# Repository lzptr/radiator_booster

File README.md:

# Radiator Booster
ESP32C3 based fan control board for a modular  [3d printed radiator booster](https://www.printables.com/model/329566-heizkorperverstarker-mit-magnethalterung-radiator-?lang=de) based on this design.
The idea is to use ESPHome with Home Assistant to turn on up to 5 radiator booster fans, when my smart thermostats are turning on, and use a Home Assistant automation to keep them running for an hour and automatically shut them off after that.

For an interactive KiCad experience see:
[Radiator Booster](https://kicanvas.org/?github=https://github.com/lzptr/radiator_booster/tree/main/hardware).

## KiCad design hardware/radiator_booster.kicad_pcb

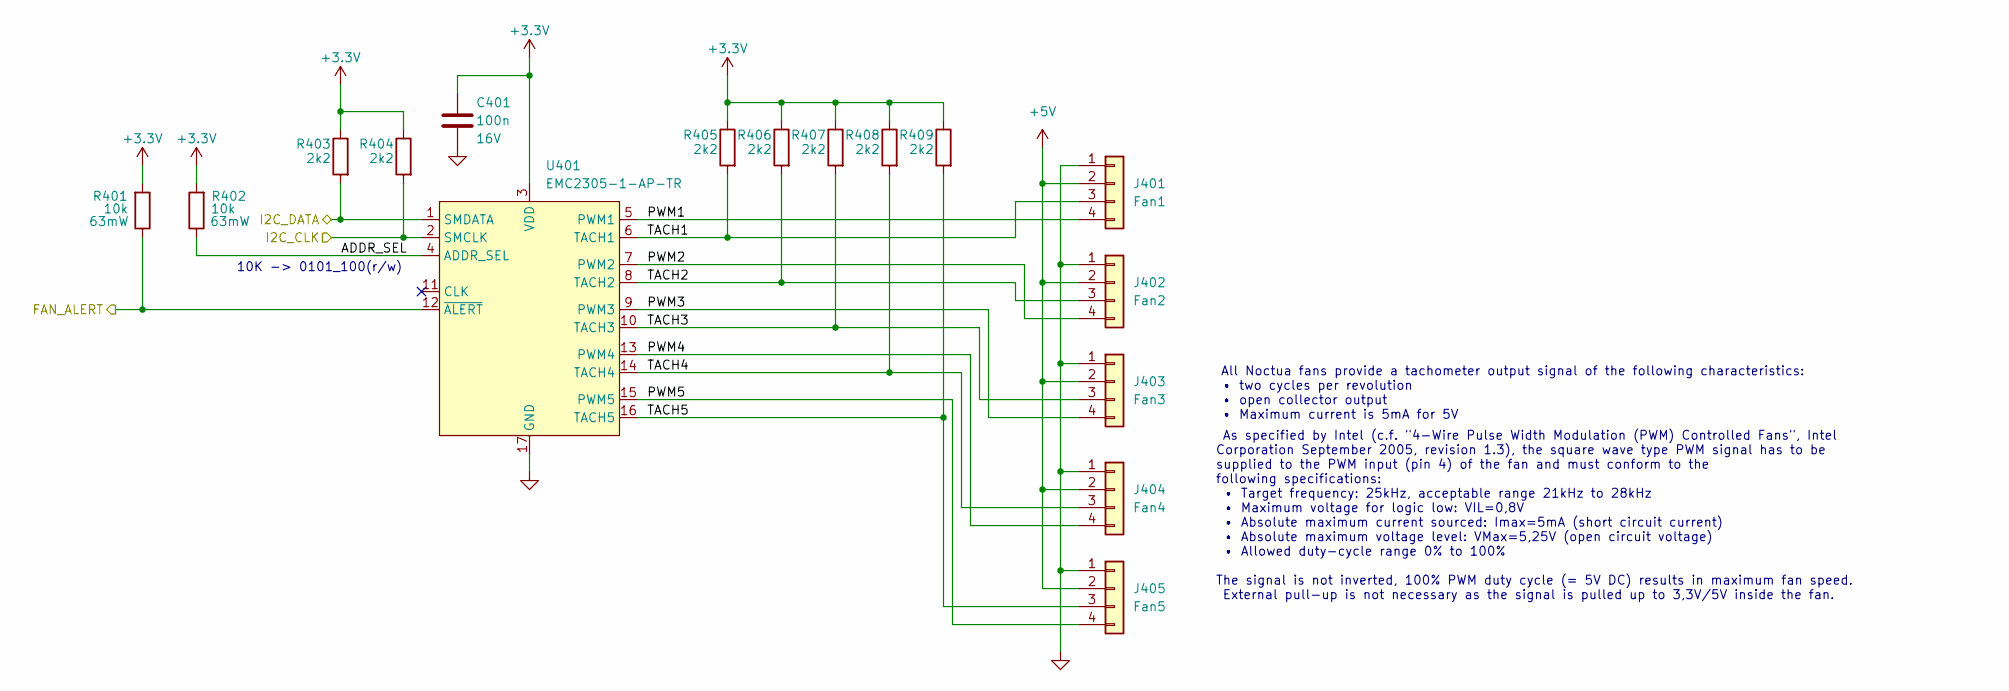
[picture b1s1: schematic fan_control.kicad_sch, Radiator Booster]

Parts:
C401: 100n; C_0402_1005Metric; Rating 16V; MPN C1525
J401: Fan1; FanPinHeader_1x04_P2.54mm_Vertical; MPN C240840
J402: Fan2; FanPinHeader_1x04_P2.54mm_Vertical; MPN C240840
J403: Fan3; FanPinHeader_1x04_P2.54mm_Vertical; MPN C240840
J404: Fan4; FanPinHeader_1x04_P2.54mm_Vertical; MPN C240840
J405: Fan5; FanPinHeader_1x04_P2.54mm_Vertical; MPN C240840
R401, R402: 10k; R_0402_1005Metric; Rating 63mW; MPN C25744
R403, R404, R405, R406, R407, R408, R409: 2k2; R_0402_1005Metric; Rating 63mW; MPN C25879
U401: EMC2305-1-AP-TR; QFN-16-1EP_4x4mm_P0.65mm_EP2.1x2.1mm

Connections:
+3.3V: C401.1, R401.2, R402.2, R403.1, R404.1, R405.1, R406.1, R407.1, R408.1, R409.1, U401.3 (VDD); also elsewhere on the board
+5V: J401.2, J402.2, J403.2, J404.2, J405.2; also elsewhere on the board
/FAN_ALERT: R401.1, U401.12 (~ALERT); also elsewhere on the board
/I2C_CLK: R404.2, U401.2 (SMCLK); also elsewhere on the board
/I2C_DATA: R403.2, U401.1 (SMDATA); also elsewhere on the board
/[4] Fan Control/ADDR_SEL: R402.1, U401.4 (ADDR_SEL)
/[4] Fan Control/PWM1: J401.4, U401.5 (PWM1)
/[4] Fan Control/PWM2: J402.4, U401.7 (PWM2)
/[4] Fan Control/PWM3: J403.4, U401.9 (PWM3)
/[4] Fan Control/PWM4: J404.4, U401.13 (PWM4)
/[4] Fan Control/PWM5: J405.4, U401.15 (PWM5)
/[4] Fan Control/TACH1: J401.3, R405.2, U401.6 (TACH1)
/[4] Fan Control/TACH2: J402.3, R406.2, U401.8 (TACH2)
/[4] Fan Control/TACH3: J403.3, R407.2, U401.10 (TACH3)
/[4] Fan Control/TACH4: J404.3, R408.2, U401.14 (TACH4)
/[4] Fan Control/TACH5: J405.3, R409.2, U401.16 (TACH5)
GND: C401.2, J401.1, J402.1, J403.1, J404.1, J405.1, U401.17 (GND); also elsewhere on the board

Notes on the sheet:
All Noctua fans provide a tachometer output signal of the following characteristics: • two cycles per revolution • open collector output • Maximum current is 5mA for 5V
10K -> 0101_100(r/w)
As specified by Intel (c.f. "4-Wire Pulse Width Modulation (PWM) Controlled Fans", Intel Corporation September 2005, revision 1.3), the square wave type PWM signal has to be supplied to the PWM input (pin 4) of the fan and must conform to the following specifications: • Target frequency: 25kHz, acc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

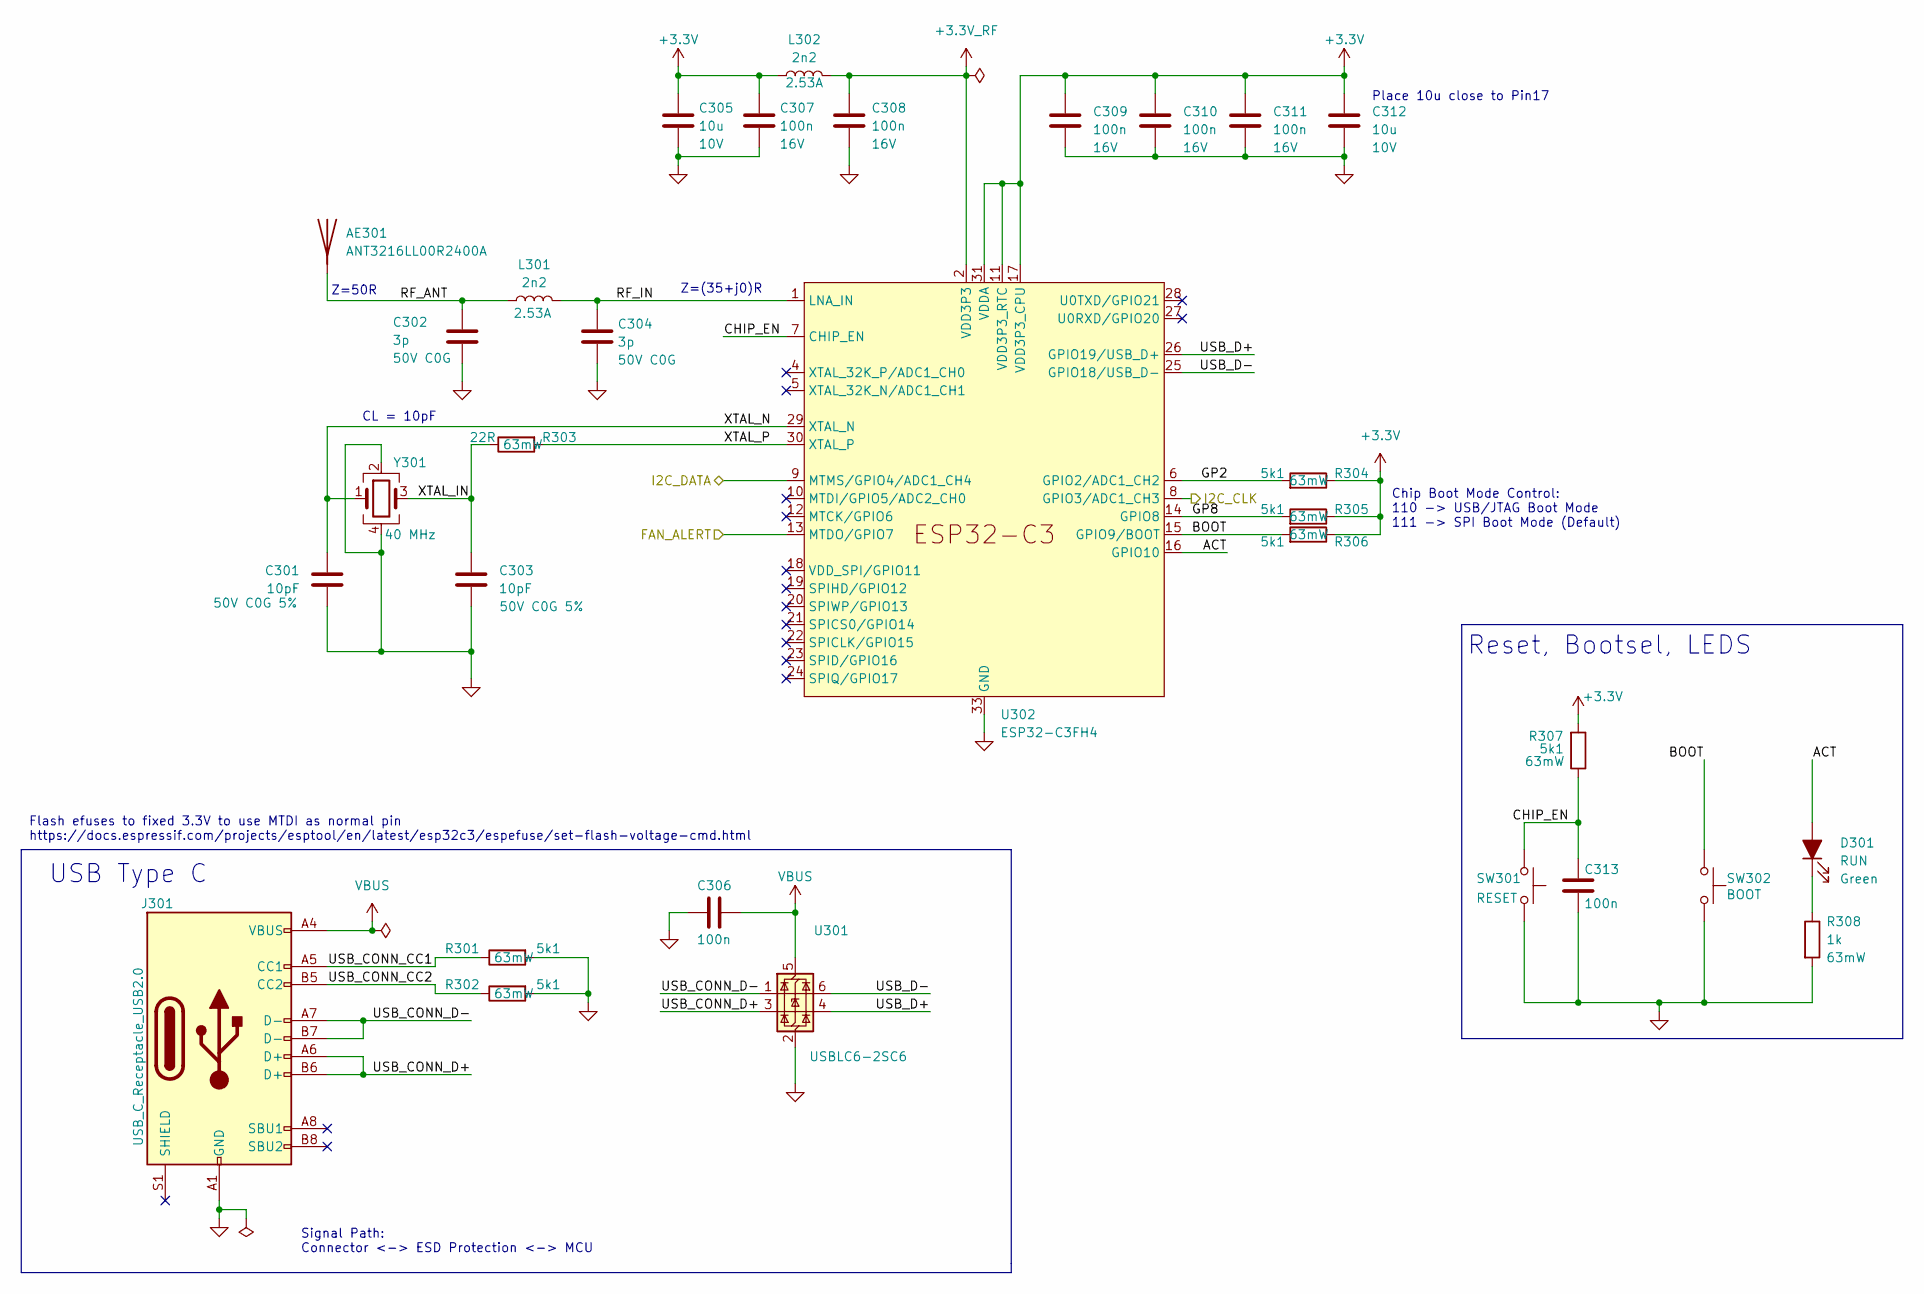
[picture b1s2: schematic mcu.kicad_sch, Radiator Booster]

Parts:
AE301: ANT3216LL00R2400A; MPN C293767
C301, C303: 10pF; C_0402_1005Metric; Rating 50V C0G 5%; MPN C32949
C302, C304: 3p; C_0402_1005Metric; Rating 50V C0G; MPN C1564
C305, C312: 10u; C_0603_1608Metric; Rating 10V; MPN C19702
C306, C307, C308, C309, C310, C311, C313: 100n; C_0402_1005Metric; Rating 16V; MPN C1525
D301: RUN; LED_0805_2012Metric; Rating Green; MPN C2297
J301: USB_C_Receptacle_USB2.0; USB_C_Receptacle_HRO_TYPE-C-31-M-12; MPN C165948
L301, L302: 2n2; L_0402_1005Metric; Rating 2.53A; MPN C412264
R301, R302, R304, R305, R306, R307: 5k1; R_0402_1005Metric; Rating 63mW; MPN C25905
R303: 22R; R_0402_1005Metric; Rating 63mW; MPN C25092
R308: 1k; R_0402_1005Metric; Rating 63mW; MPN C11702
SW301: RESET; SW_TL3365AF180QG; MPN C2886926
SW302: BOOT; SW_TL3365AF180QG; MPN C2886926
U301: USBLC6-2SC6; SOT-23-6; MPN C5261088
U302: ESP32-C3FH4; QFN-32-1EP_5x5mm_P0.5mm_EP3.45x3.45mm; MPN C2858491
Y301: 40 MHz; Crystal_SMD_2520-4Pin_2.5x2.0mm; MPN C426970

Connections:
+3.3V: C305.1, C307.1, C309.1, C310.1, C311.1, C312.1, L302.1, R304.1, R305.1, R306.1, R307.2, U302.11 (VDD3P3_RTC), U302.17 (VDD3P3_CPU), U302.31 (VDDA), U302.32 (VDDA); also elsewhere on the board
+3.3V_RF: C308.1, L302.2, U302.2 (VDD3P3), U302.3 (VDD3P3)
/FAN_ALERT: U302.13 (MTDO/GPIO7); also elsewhere on the board
/I2C_CLK: U302.8 (GPIO3/ADC1_CH3); also elsewhere on the board
/I2C_DATA: U302.9 (MTMS/GPIO4/ADC1_CH4); also elsewhere on the board
/[3] MCU/ACT: D301.2 (A), U302.16 (GPIO10)
/[3] MCU/BOOT: R306.2, SW302.1, U302.15 (GPIO9/BOOT)
/[3] MCU/CHIP_EN: C313.1, R307.1, SW301.1, U302.7 (CHIP_EN)
/[3] MCU/GP2: R304.2, U302.6 (GPIO2/ADC1_CH2)
/[3] MCU/GP8: R305.2, U302.14 (GPIO8)
/[3] MCU/RF_ANT: AE301.1 (A), C302.1, L301.1
/[3] MCU/RF_IN: C304.1, L301.2, U302.1 (LNA_IN)
/[3] MCU/USB_CONN_CC1: J301.A5 (CC1), R301.1
/[3] MCU/USB_CONN_CC2: J301.B5 (CC2), R302.1
/[3] MCU/USB_CONN_D+: J301.A6 (D+), J301.B6 (D+), U301.3 (I/O2)
/[3] MCU/USB_CONN_D-: J301.A7 (D-), J301.B7 (D-), U301.1 (I/O1)
/[3] MCU/USB_D+: U301.4 (I/O2), U302.26 (GPIO19/USB_D+)
/[3] MCU/USB_D-: U301.6 (I/O1), U302.25 (GPIO18/USB_D-)
/[3] MCU/XTAL_IN: C303.1, R303.1, Y301.3
/[3] MCU/XTAL_N: C301.1, U302.29 (XTAL_N), Y301.1
/[3] MCU/XTAL_P: R303.2, U302.30 (XTAL_P)
GND: C301.2, C302.2, C303.2, C304.2, C305.2, C306.2, C307.2, C308.2, C309.2, C310.2, C311.2, C312.2, C313.2, J301.A1 (GND), J301.A12 (GND), J301.B1 (GND), J301.B12 (GND), R301.2, R302.2, R308.2, SW301.2, SW302.2, U301.2 (GND), U302.33 (GND), Y301.2, Y301.4; also elsewhere on the board
unnamed: D301.1 (K), R308.1
VBUS: C306.1, J301.A4 (VBUS), J301.A9 (VBUS), J301.B4 (VBUS), J301.B9 (VBUS), U301.5 (VBUS); also elsewhere on the board

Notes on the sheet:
Z=50R
CL = 10pF
Chip Boot Mode Control: 110 -> USB/JTAG Boot Mode 111 -> SPI Boot Mode (Default)
Z=(35+j0)R
Reset, Bootsel, LEDS
Flash efuses to fixed 3.3V to use MTDI as normal pin https://docs.espressif.com/projects/esptool/en/latest/esp32c3/espefuse/set-flash-voltage-cmd.html
USB Type C
Signal Path: Connector <-> ESD Protection <-> MCU
Place 10u close to Pin17

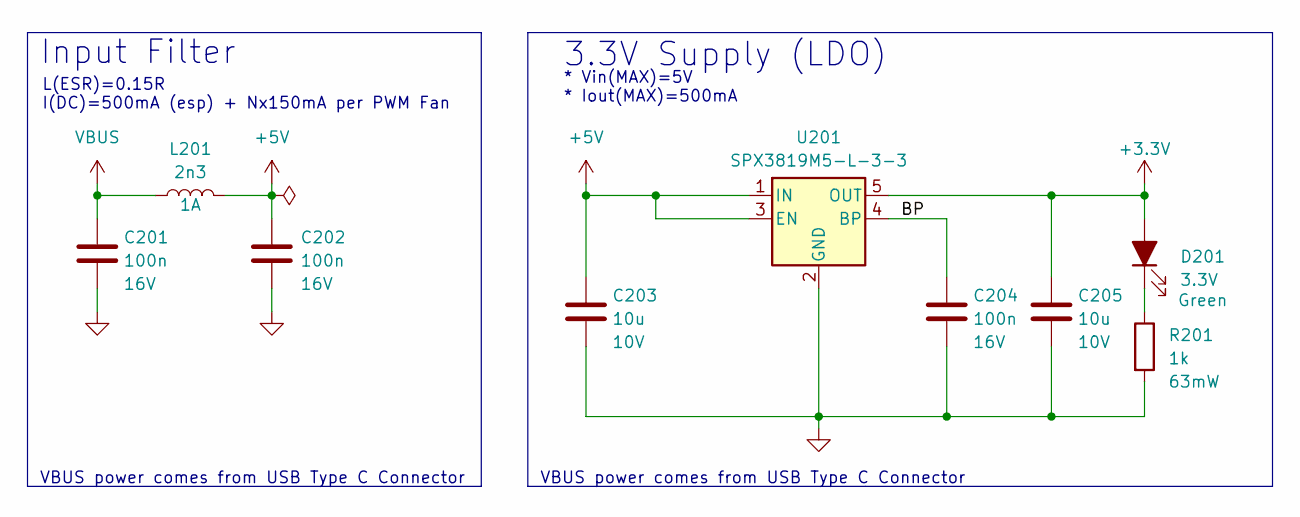
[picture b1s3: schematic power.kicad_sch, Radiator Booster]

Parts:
C201, C202, C204: 100n; C_0402_1005Metric; Rating 16V; MPN C1525
C203, C205: 10u; C_0603_1608Metric; Rating 10V; MPN C19702
D201: 3.3V; LED_0805_2012Metric; Rating Green; MPN C2297
L201: 2n3; L_0402_1005Metric; Rating 1A; MPN C412340
R201: 1k; R_0402_1005Metric; Rating 63mW; MPN C11702
U201: SPX3819M5-L-3-3; SOT-23-5; MPN C9055

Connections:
+3.3V: C205.1, D201.2 (A), U201.5 (OUT); also elsewhere on the board
+5V: C202.1, C203.1, L201.2, U201.1 (IN), U201.3 (EN); also elsewhere on the board
/[2] Power/BP: C204.1, U201.4 (BP)
GND: C201.2, C202.2, C203.2, C204.2, C205.2, R201.2, U201.2 (GND); also elsewhere on the board
unnamed: D201.1 (K), R201.1
VBUS: C201.1, L201.1; also elsewhere on the board

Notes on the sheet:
Input Filter
* Vin(MAX)=5V * Iout(MAX)=500mA
VBUS power comes from USB Type C Connector
L(ESR)=0.15R I(DC)=500mA (esp) + Nx150mA per PWM Fan
3.3V Supply (LDO)

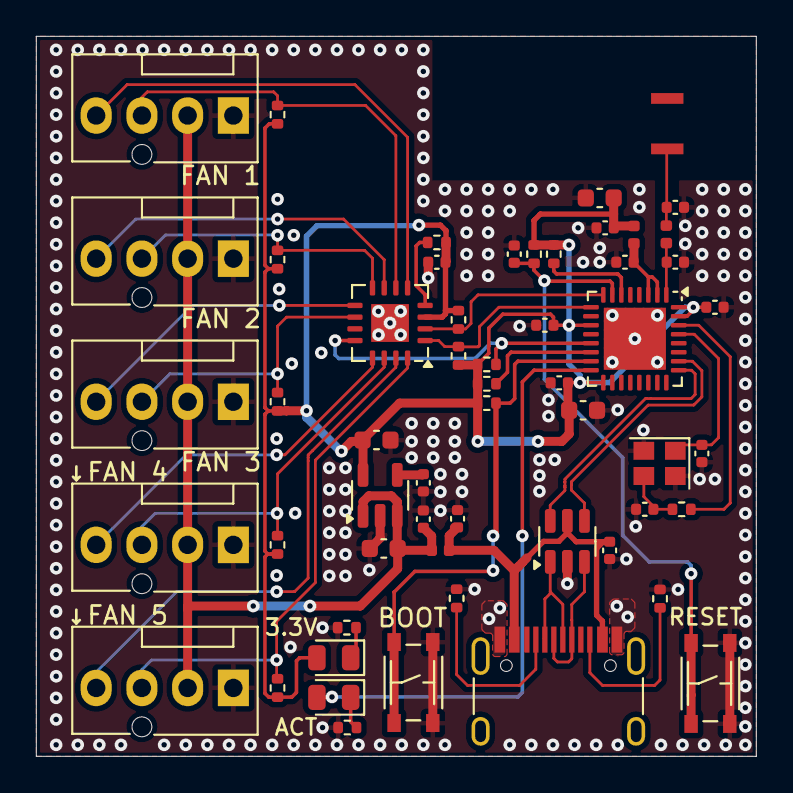
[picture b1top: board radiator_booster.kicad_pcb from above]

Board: 4 copper layers, 40.0 x 40.0 mm, 56 parts (0 on the bottom side), 38 nets.

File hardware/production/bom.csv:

Designator,Footprint,Quantity,Value,LCSC Part #
AE301,ANT3216LL00R2400A,1,ANT3216LL00R2400A,C293767
"C201, C202, C204, C306, C307, C308, C309, C310, C311, C313, C401",0402,11,100n,C1525
"C203, C205, C305, C312",0603,4,10u,C19702
"C301, C303",0402,2,10pF,C32949
"C302, C304",0402,2,3p,C1564
D201,0805,1,3.3V,C2297
D301,0805,1,RUN,C2297
J301,USB_C_Receptacle_HRO_TYPE-C-31-M-12,1,USB_C_Receptacle_USB2.0,C165948
J401,FanPinHeader_1x04_P2.54mm_Vertical,1,Fan1,C240840
J402,FanPinHeader_1x04_P2.54mm_Vertical,1,Fan2,C240840
J403,FanPinHeader_1x04_P2.54mm_Vertical,1,Fan3,C240840
J404,FanPinHeader_1x04_P2.54mm_Vertical,1,Fan4,C240840
J405,FanPinHeader_1x04_P2.54mm_Vertical,1,Fan5,C240840
"L201, L301, L302",0402,3,2n2,C412264
"R201, R308",0402,2,1k,C11702
"R301, R302, R304, R305, R306, R307",0402,6,5k1,C25905
R303,0402,1,22R,C25092
"R401, R402",0402,2,10k,C25744
"R403, R404, R405, R406, R407, R408, R409",0402,7,2k2,C25879
SW301,SW_TL3365AF180QG,1,RESET,C2886926
SW302,SW_TL3365AF180QG,1,BOOT,C2886926
U201,SOT-23-5,1,SPX3819M5-L-3-3,C9055
U301,SOT-23-6,1,USBLC6-2SC6,C5261088
U302,QFN-32-1EP_5x5mm_P0.5mm_EP3.45x3.45mm,1,ESP32-C3FH4,C2858491
U401,QFN-16-1EP_4x4mm_P0.65mm_EP2.1x2.1mm,1,EMC2305-1-AP-TR,
Y301,Crystal_SMD_2520-4Pin_2.5x2.0mm,1,40 MHz,C426970

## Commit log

2024-12-20 Finished the schematic
2024-12-29 WIP pcb layout
2025-01-11 Finished the pcb layout
2025-01-19 release: v0.1
2025-01-31 Added esphome component code for the emc2305 and an example yaml
2025-01-31 Fixing paths
2025-02-22 Added esphome firmware and external component
2025-03-08 Started work on rev 0.2
2025-03-09 Fixed routing at intel pwm fan connectors
2025-03-17 Finished layout for rev 0.2
2025-03-18 Final touches
2025-03-18 Added production files
2025-03-18 Updated readme image
2025-03-22 Updated matching network. Changed inductor for all filter for bom sonsolidation after matching network changes
